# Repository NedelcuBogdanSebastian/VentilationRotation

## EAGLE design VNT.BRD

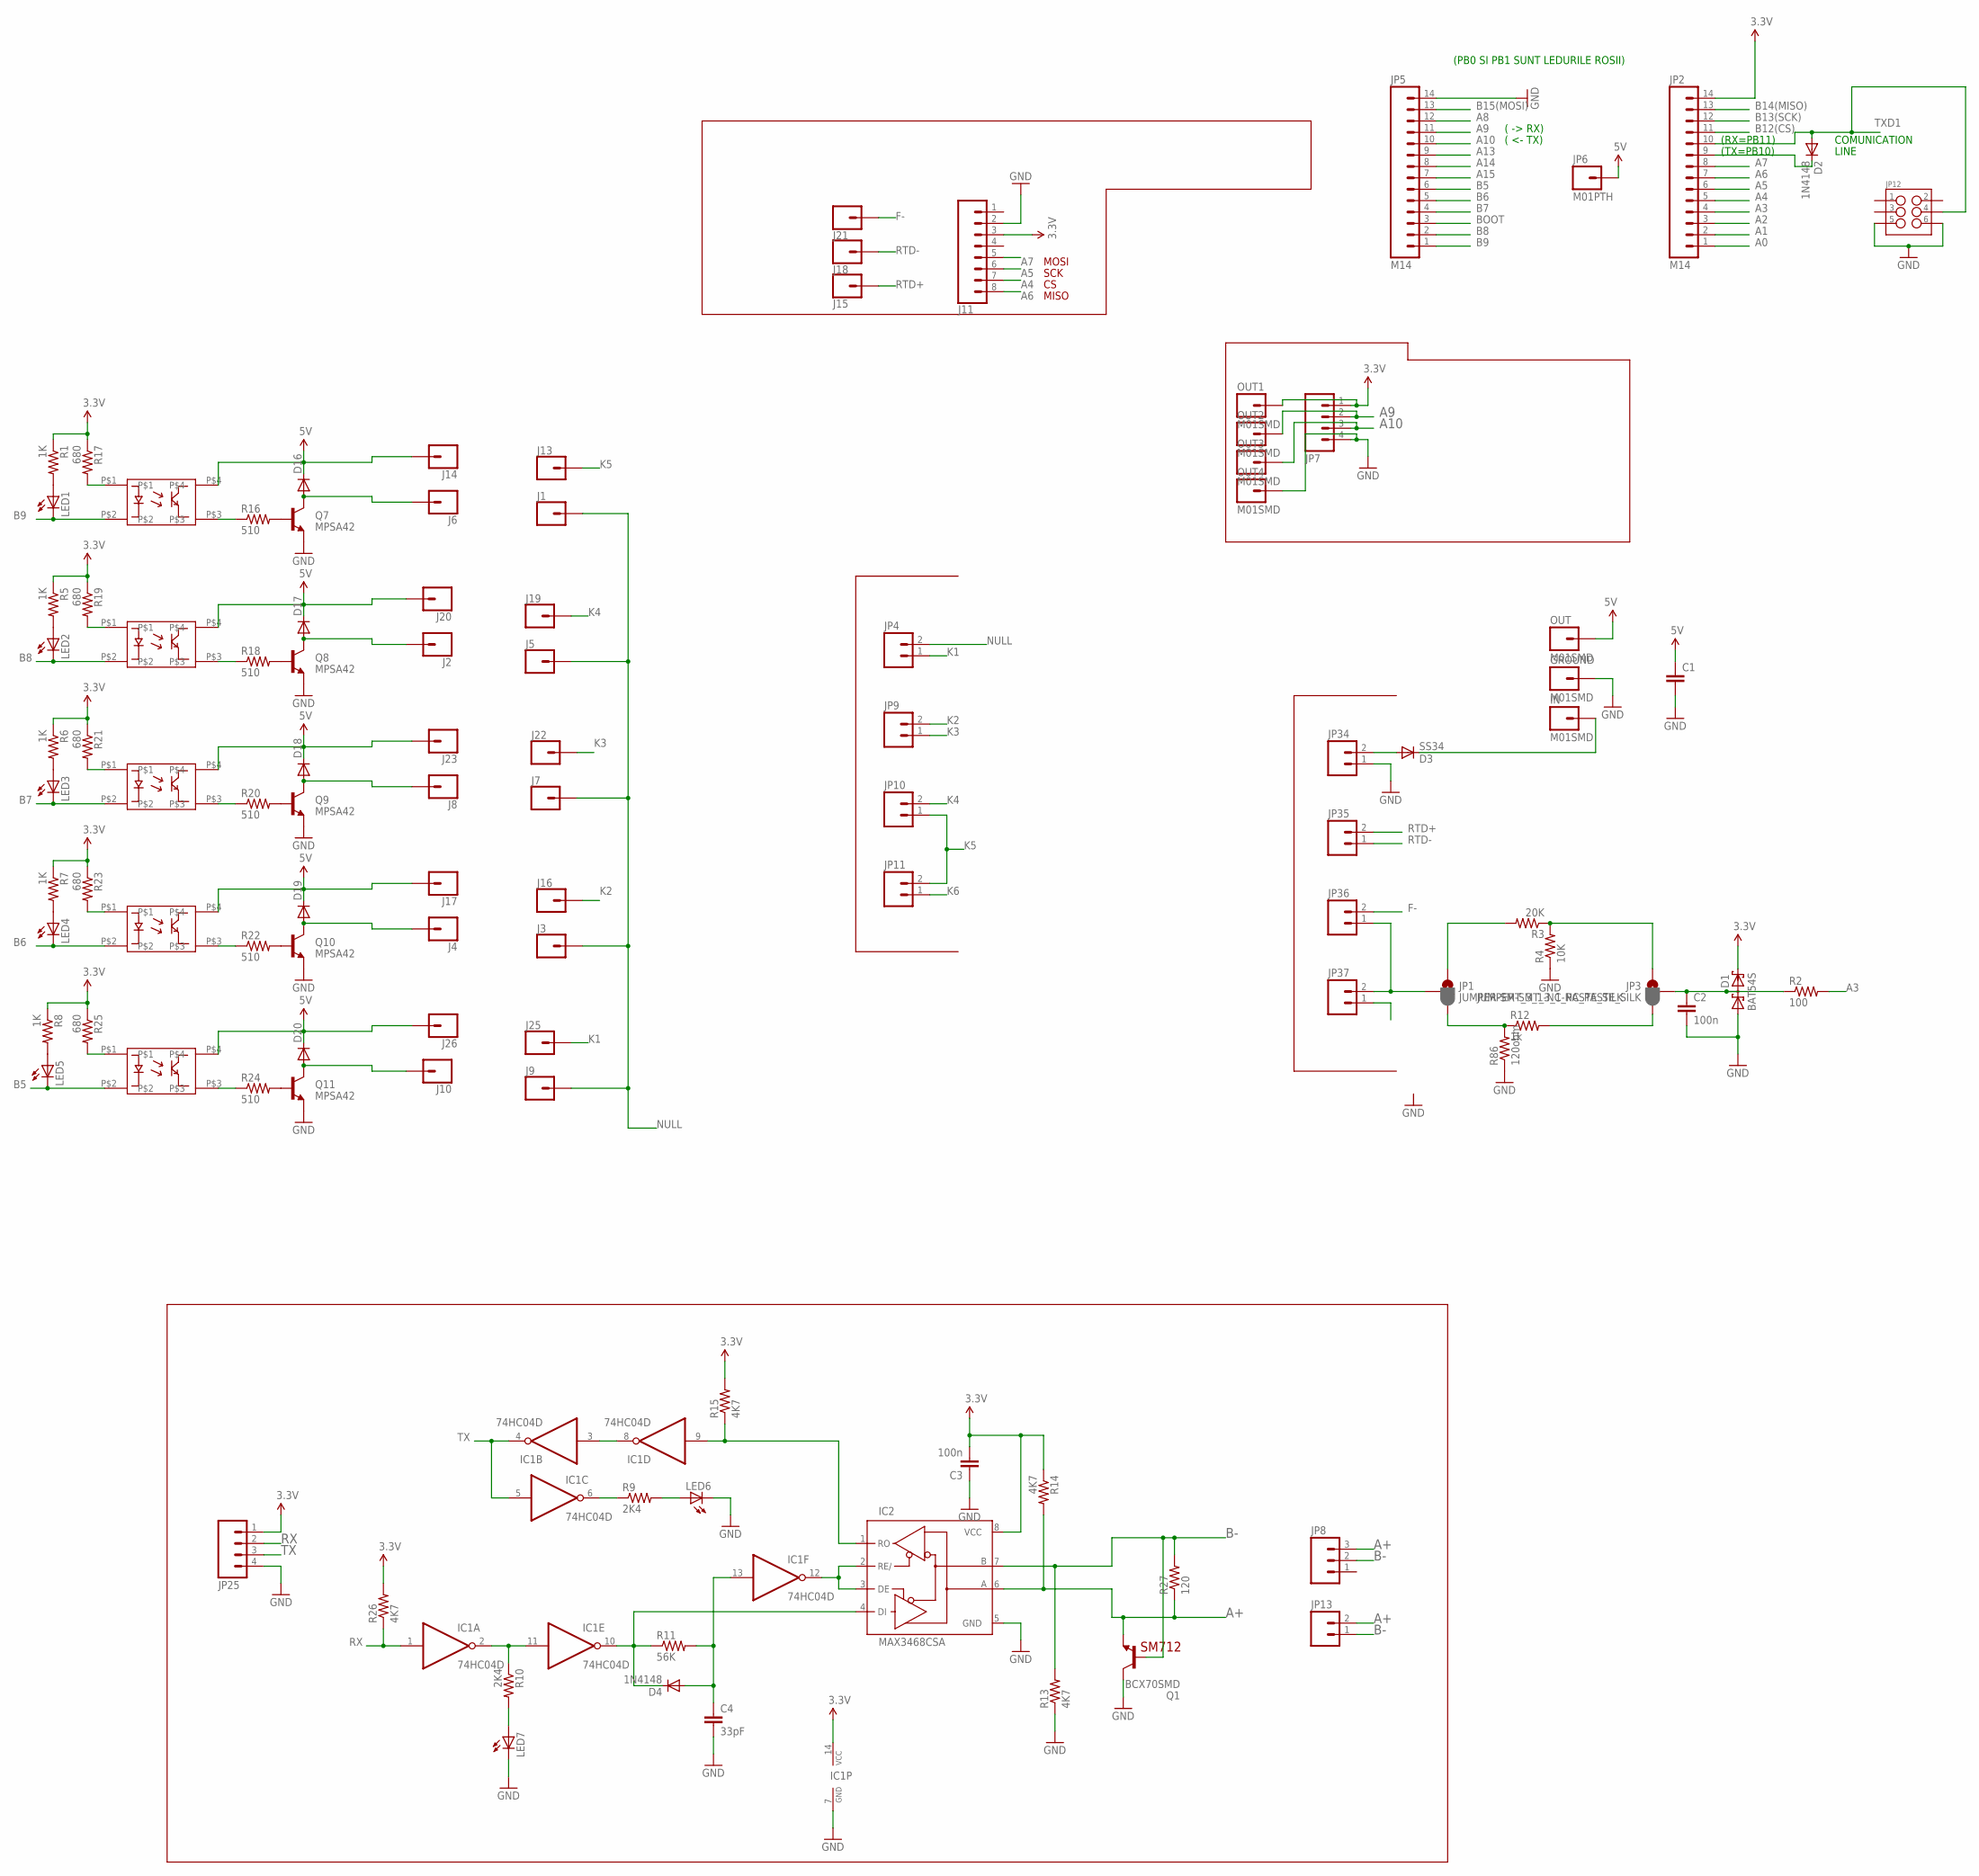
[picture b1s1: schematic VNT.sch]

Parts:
C1: CAPPTH1; CAP-PTH-5MM
C2, C3: 100n; 0805
C4: 33pF; 0805
D1: BAT54S; SOT23
D2, D4: 1N4148; MINIMELF
D3: SS34; SMC
D16, D17, D18, D19, D20: DIODE-MINIMELF; MINIMELF
GROUND: M01SMD; LUXEON-PAD
IC1: 74HC04D; SO14
IC2: MAX3468CSA; SO08
IN: M01SMD; LUXEON-PAD
J1, J2, J3, J4, J5, J6, J7, J8, J9, J10, J13, J14, J15, J16, J17, J18, J19, J20, J21, J22, J23, J25, J26: CONN_01; 1X01@2
J11: CONN_08LOCK; 1X08_LOCK
JP1, JP3: JUMPER-SMT_3_1-NC_PASTE_SILK; SMT-JUMPER_3_1-NC_PASTE_SILK
JP2, JP5: M14; 1X14
JP4, JP9, JP10, JP11, JP13, JP34, JP35, JP36, JP37: M025MM; SCREWTERMINAL-5MM-2
JP6: M01PTH; 1X01
JP7, JP25: M04PTH; 1X04
JP8: M03-SCREW-5MM; SCREWTERMINAL-5MM-3
JP12: M03X22X3_SILK_MALE_PTH; 2X3
LED1, LED2, LED3, LED4, LED5, LED6, LED7: LEDCHIP-LED0805; CHIP-LED0805
OUT, OUT1, OUT2, OUT3, OUT4: M01SMD; LUXEON-PAD
Q1: BCX70SMD; SOT23
Q7, Q8, Q9, Q10, Q11: MPSA42; SOT23-3
R1, R5, R6, R7, R8: 1K; 0805
R2: 100; 0805
R3: 20K; 1206
R4: 10K; 1206
R9, R10: 2K4; 0805
R11: 56K; 0805
R12: 1k; 0805
R13, R14, R15, R26: 4K7; 0805
R16, R18, R20, R22, R24: 510; 0805
R17, R19, R21, R23, R25: 680; 0805
R27: 120; 0805
R86: 120ohm; R2010
U$13, U$14, U$15, U$16, U$17: IS181D-I; TLP181-I

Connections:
3.3V: C3.2, D1.2 (C2), IC1.14 (VCC), IC2.8 (VCC), J11.3, JP2.14, JP7.1, JP25.1, OUT1.P$1, R1.1, R5.1, R6.1, R7.1, R8.1, R14.1, R15.2, R17.1, R19.1, R21.1, R23.1, R25.1, R26.2
5V: C1.1, D16.C, D17.C, D18.C, D19.C, D20.C, J14.1, J17.1, J20.1, J23.1, J26.1, JP6.1, OUT.P$1, U$13.P$4, U$14.P$4, U$15.P$4, U$16.P$4, U$17.P$4
A0: JP2.1
A1: JP2.2
A2: JP2.3
A3: JP2.4, R2.2
A4: J11.7, JP2.5
A5: J11.6, JP2.6
A6: J11.8, JP2.7
A7: J11.5, JP2.8
A8: JP5.12
A9: JP5.11, JP7.2, OUT2.P$1
A10: JP5.10, JP7.3, OUT3.P$1
A13: JP5.9
A14: JP5.8
A15: JP5.7
A+: IC2.6 (A), JP8.3, JP13.2, Q1.2 (E), R14.2, R27.1
B5: JP5.6, LED5.C, U$17.P$2
B6: JP5.5, LED4.C, U$16.P$2
B7: JP5.4, LED3.C, U$15.P$2
B8: JP5.2, LED2.C, U$13.P$2
B9: JP5.1, LED1.C, U$14.P$2
B12(CS): JP2.11
B13(SCK): JP2.12
B14(MISO): JP2.13
B15(MOSI): JP5.13
B-: IC2.7 (B), JP8.2, JP13.1, Q1.1 (B), R13.2, R27.2
BOOT: JP5.3
F-: J21.1, JP36.2
GND: C1.2, C2.2, C3.1, C4.2, D1.1 (A1), GROUND.P$1, IC1.7 (GND), IC2.5 (GND), J11.2, JP5.14, JP7.4, JP12.5, JP12.6, JP25.4, JP34.1, LED6.C, LED7.C, OUT4.P$1, Q1.3 (C), Q7.2 (E), Q8.2 (E), Q9.2 (E), Q10.2 (E), Q11.2 (E), R4.1, R13.1, R86.1
K1: J25.1, JP4.1
K2: J16.1, JP9.2
K3: J22.1, JP9.1
K4: J19.1, JP10.2
K5: J13.1, JP10.1, JP11.2
K6: JP11.1
unnamed: LED1.A, R1.2
unnamed: LED2.A, R5.2
unnamed: LED3.A, R6.2
unnamed: D3.A, JP34.2
unnamed: JP3.3, R12.2
unnamed: JP3.1, R3.1, R4.2
unnamed: C2.1, D1.3 (C1A2), JP3.2, R2.1
unnamed: JP1.1, R3.2
unnamed: LED4.A, R7.2
unnamed: LED5.A, R8.2
unnamed: D3.C, IN.P$1
unnamed: LED7.A, R10.2
unnamed: LED6.A, R9.2
unnamed: IC1.2 (O), IC1.11 (I), R10.1
unnamed: IC1.9 (I), IC2.1 (RO), R15.1
unnamed: JP1.2, JP36.1, JP37.2
unnamed: IC1.3 (I), IC1.8 (O)
unnamed: C4.1, D4.A, IC1.13 (I), R11.2
unnamed: IC1.6 (O), R9.1
unnamed: D4.C, IC1.10 (O), IC2.4 (DI), R11.1
unnamed: IC1.12 (O), IC2.2 (RE/), IC2.3 (DE)
unnamed: Q7.1 (B), R16.2
unnamed: D16.A, J6.1, Q7.3 (C)
unnamed: Q8.1 (B), R18.2
unnamed: D17.A, J2.1, Q8.3 (C)
unnamed: Q9.1 (B), R20.2
unnamed: D18.A, J8.1, Q9.3 (C)
unnamed: Q10.1 (B), R22.2
unnamed: D19.A, J4.1, Q10.3 (C)
unnamed: Q11.1 (B), R24.2
unnamed: D20.A, J10.1, Q11.3 (C)
unnamed: R16.1, U$14.P$3
unnamed: R17.2, U$14.P$1
unnamed: R18.1, U$13.P$3
unnamed: R20.1, U$15.P$3
unnamed: R22.1, U$16.P$3
unnamed: R24.1, U$17.P$3
unnamed: R19.2, U$13.P$1
unnamed: R21.2, U$15.P$1
unnamed: R23.2, U$16.P$1
unnamed: R25.2, U$17.P$1
unnamed: JP1.3, R12.1, R86.2
NULL: J1.1, J3.1, J5.1, J7.1, J9.1, JP4.2
RTD+: J15.1, JP35.2
RTD-: J18.1, JP35.1
RX: IC1.1 (I), JP25.2, R26.1
RXD1: D2.C, JP2.9
TX: IC1.4 (O), IC1.5 (I), JP25.3
TXD1: D2.A, JP2.10, JP12.4

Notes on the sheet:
COMUNICATION
LINE
( -> RX)
( <- TX)
(PB0 SI PB1 SUNT LEDURILE ROSII)
(RX=PB11)
(TX=PB10)
MISO
SCK
MOSI
SM712

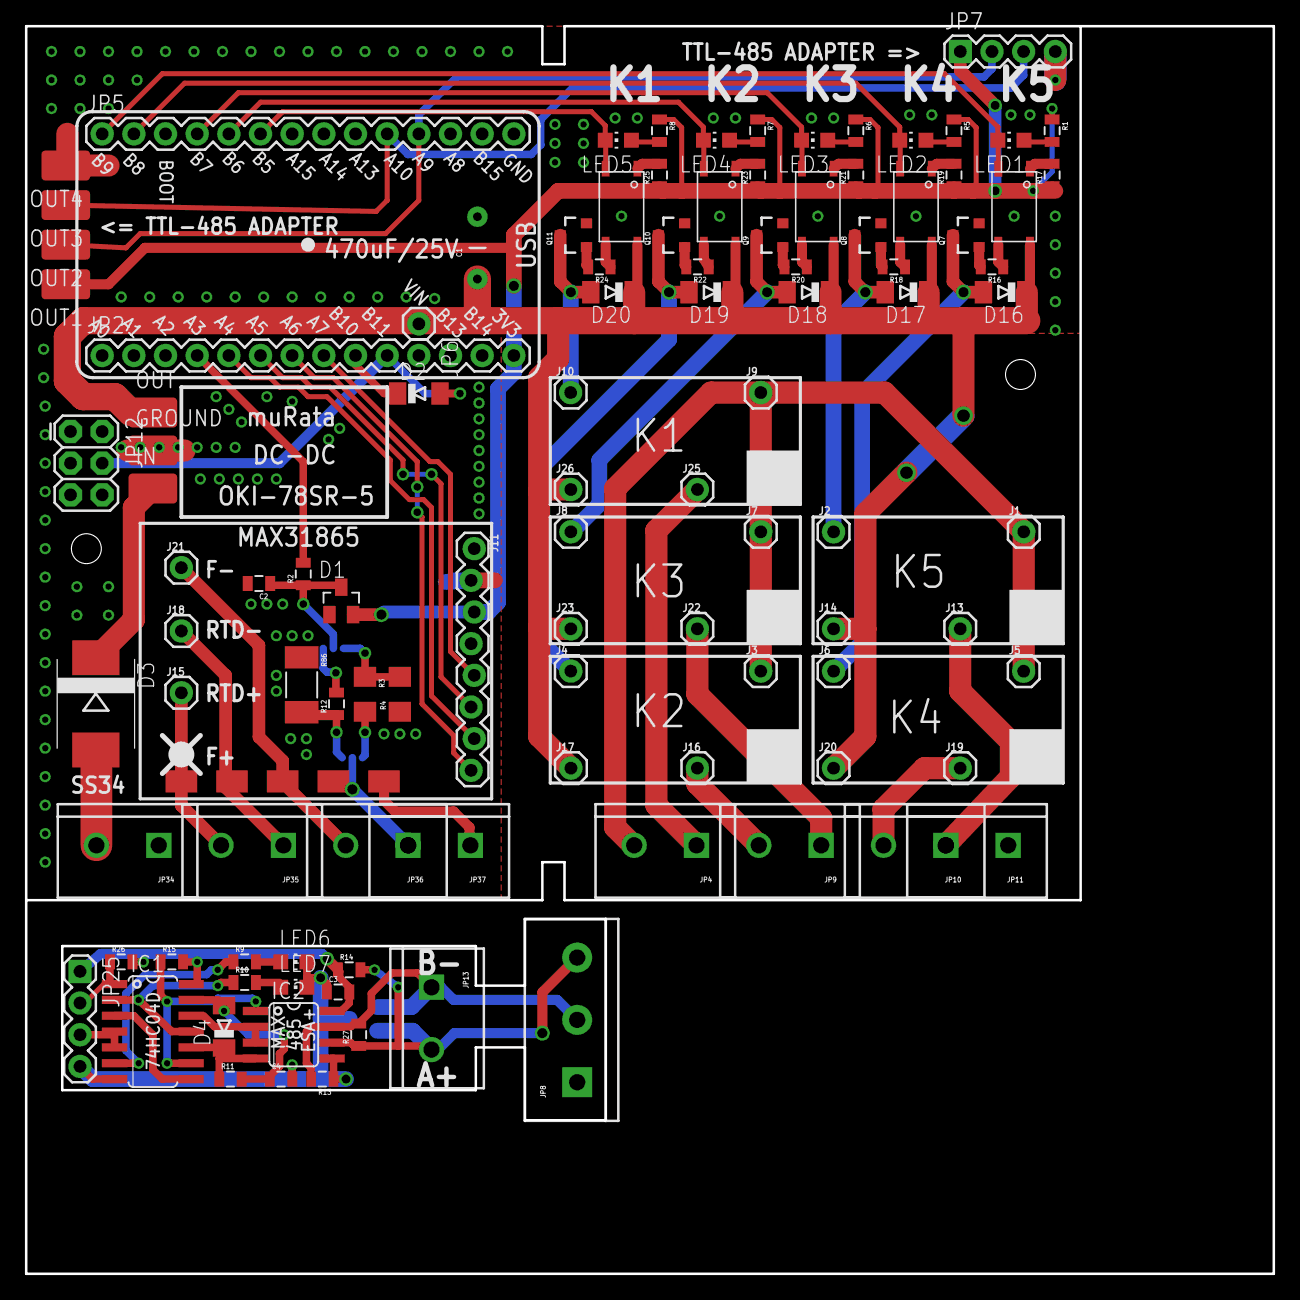
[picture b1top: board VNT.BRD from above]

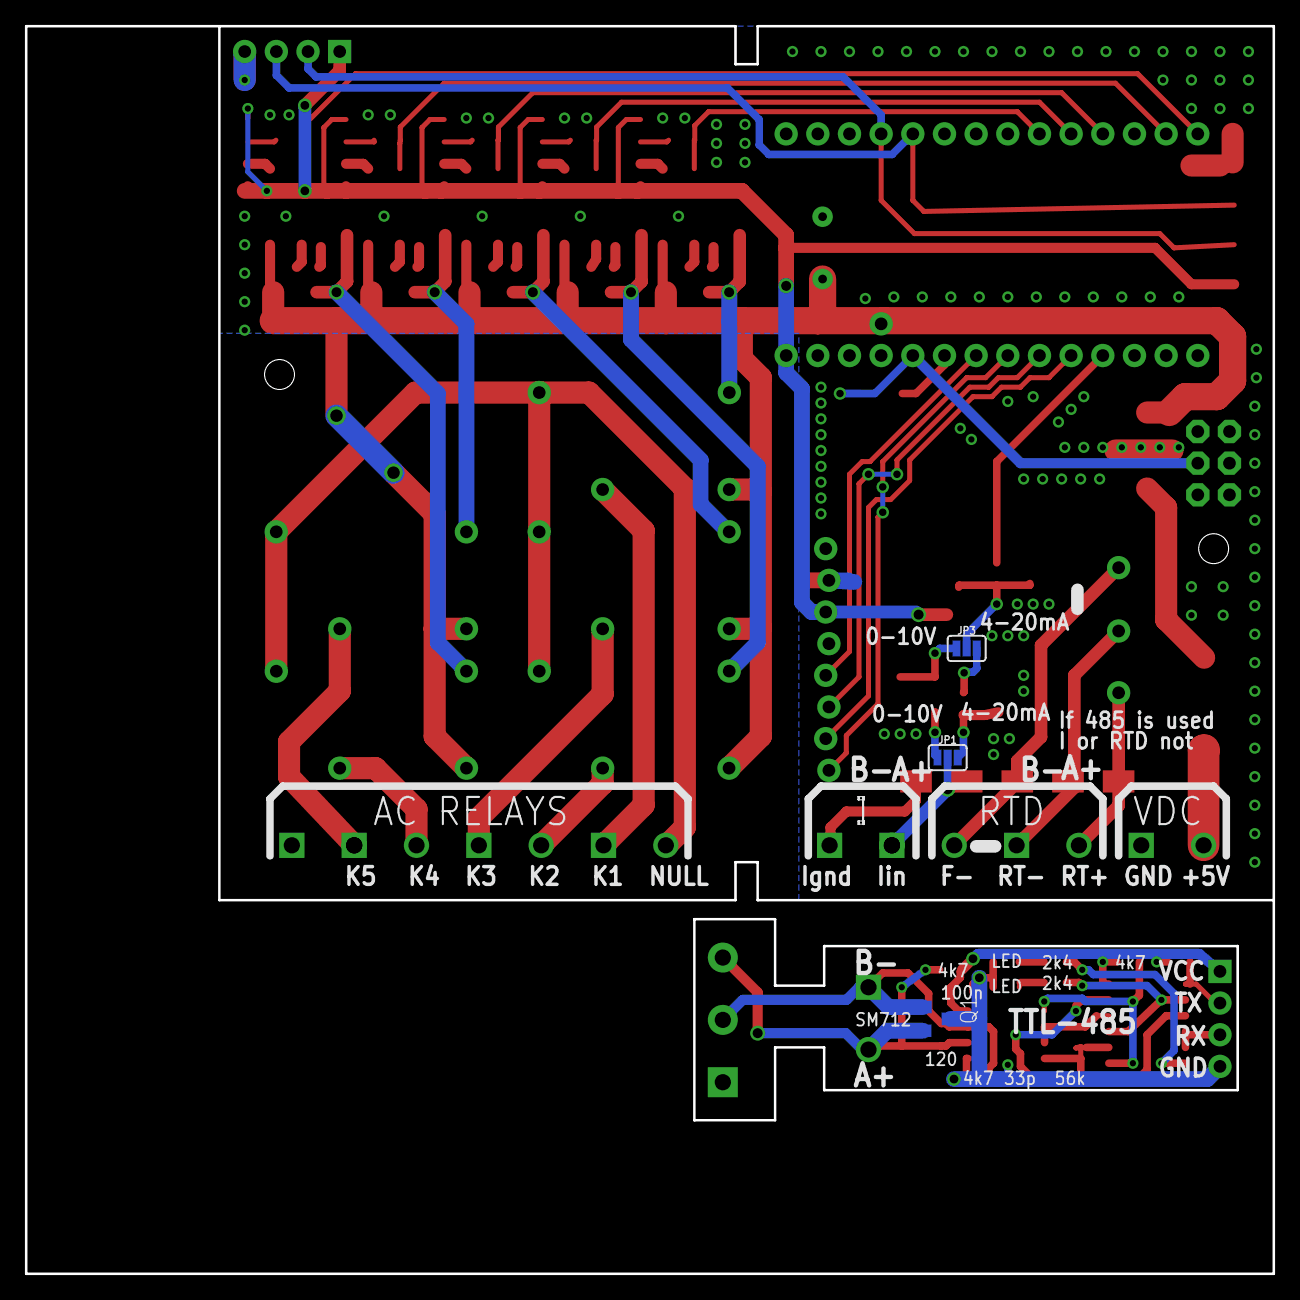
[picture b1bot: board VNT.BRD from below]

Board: 2 copper layers, 100.1 x 100.1 mm, 110 parts (3 on the bottom side), 72 nets.

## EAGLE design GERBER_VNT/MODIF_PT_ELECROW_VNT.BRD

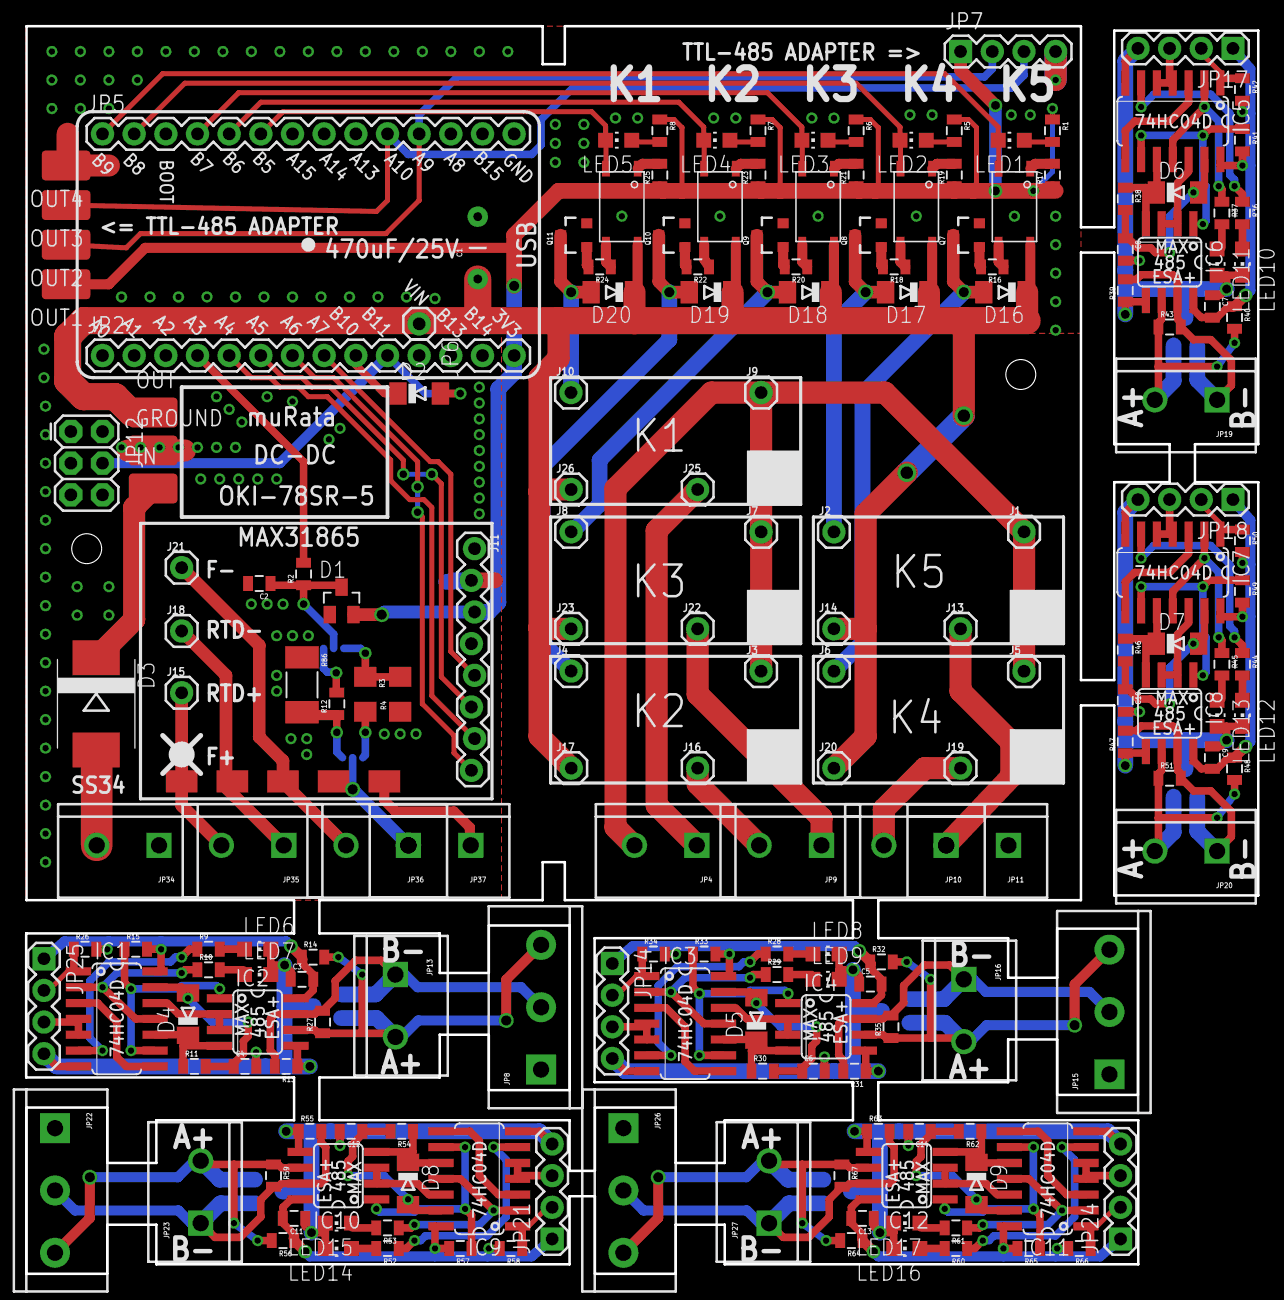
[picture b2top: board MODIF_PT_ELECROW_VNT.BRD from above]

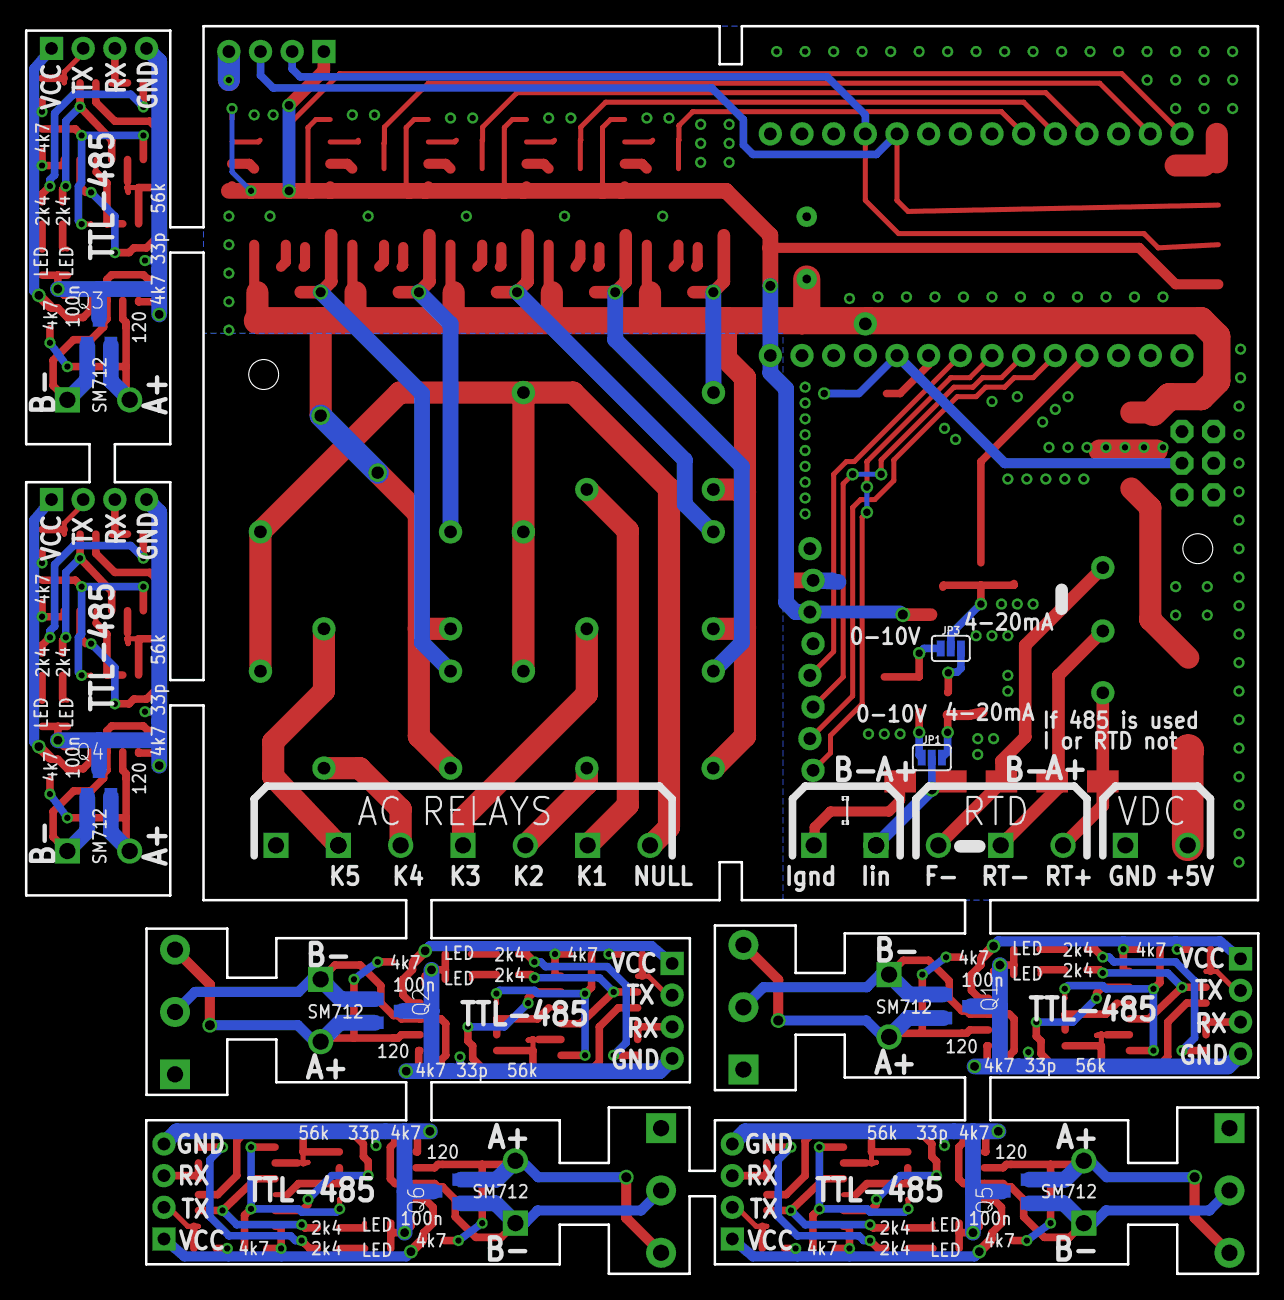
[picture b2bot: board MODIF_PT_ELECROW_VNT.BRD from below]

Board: 2 copper layers, 98.8 x 100.1 mm, 203 parts (8 on the bottom side), 148 nets.

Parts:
C1: CAP-PTH-5MM
C2, C3, C5, C7, C9, C11, C13: 100n; 0805
C4, C6, C8, C10, C12, C14: 33pF; 0805
D1: BAT54S; SOT23
D2, D4, D5, D6, D7, D8, D9: 1N4148; MINIMELF
D3: SS34; SMC
D16, D17, D18, D19, D20: MINIMELF
GROUND: M01SMD; LUXEON-PAD
IC1, IC3, IC5, IC7, IC9, IC11: 74HC04D; SO14
IC2, IC4, IC6, IC8, IC10, IC12: MAX3468CSA; SO08
IN: M01SMD; LUXEON-PAD
J1, J2, J3, J4, J5, J6, J7, J8, J9, J10, J13, J14, J15, J16, J17, J18, J19, J20, J21, J22, J23, J25, J26: 1X01@2
J11: 1X08_LOCK
JP1, JP3: JUMPER-SMT_3_1-NC_PASTE_SILK; SMT-JUMPER_3_1-NC_PASTE_SILK
JP2, JP5: M14; 1X14
JP4, JP9, JP10, JP11, JP13, JP16, JP19, JP20, JP23, JP27, JP34, JP35, JP36, JP37: SCREWTERMINAL-5MM-2
JP6: M01PTH; 1X01
JP7, JP14, JP17, JP18, JP21, JP24, JP25: 1X04
JP8, JP15, JP22, JP26: SCREWTERMINAL-5MM-3
JP12: 2X3
LED1, LED2, LED3, LED4, LED5, LED6, LED7, LED8, LED9, LED10, LED11, LED12, LED13, LED14, LED15, LED16, LED17: CHIP-LED0805
OUT, OUT1, OUT2, OUT3, OUT4: M01SMD; LUXEON-PAD
Q1, Q2, Q3, Q4, Q5, Q6: BCX70SMD; SOT23
Q7, Q8, Q9, Q10, Q11: MPSA42; SOT23-3
R1, R5, R6, R7, R8: 1K; 0805
R2: 100; 0805
R3: 20K; 1206
R4: 10K; 1206
R9, R10, R28, R29, R36, R37, R44, R45, R52, R53, R60, R61: 2K4; 0805
R11, R30, R38, R46, R54, R62: 56K; 0805
R12: 1k; 0805
R13, R14, R15, R26, R31, R32, R33, R34, R39, R40, R41, R42, R47, R48, R49, R50, R55, R56, R57, R58, R63, R64, R65, R66: 4K7; 0805
R16, R18, R20, R22, R24: 510; 0805
R17, R19, R21, R23, R25: 680; 0805
R27, R35, R43, R51, R59, R67: 120; 0805
R86: 120ohm; R2010
U$13, U$14, U$15, U$16, U$17: IS181D-I; TLP181-I

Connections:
3.3V: D1.2, J11.3, JP2.14, JP7.1, OUT1.P$1, R1.1, R5.1, R6.1, R7.1, R8.1, R17.1, R19.1, R21.1, R23.1, R25.1
3.3V1: C5.2, IC3.14, IC4.8, JP14.1, R32.1, R33.2, R34.2
3.3V2: C7.2, IC5.14, IC6.8, JP17.1, R40.1, R41.2, R42.2
3.3V3: C9.2, IC7.14, IC8.8, JP18.1, R48.1, R49.2, R50.2
3.3V4: C11.2, IC9.14, IC10.8, JP21.1, R56.1, R57.2, R58.2
3.3V5: C13.2, IC11.14, IC12.8, JP24.1, R64.1, R65.2, R66.2
5V: C1.1, D16.C, D17.C, D18.C, D19.C, D20.C, J14.1, J17.1, J20.1, J23.1, J26.1, JP6.1, OUT.P$1, U$13.P$4, U$14.P$4, U$15.P$4, U$16.P$4, U$17.P$4
A3: JP2.4, R2.2
A4: J11.7, JP2.5
A5: J11.6, JP2.6
A6: J11.8, JP2.7
A7: J11.5, JP2.8
A9: JP5.11, JP7.2, OUT2.P$1
A10: JP5.10, JP7.3, OUT3.P$1
A+: IC2.6, JP8.3, JP13.2, Q1.2, R14.2, R27.1
A+1: IC4.6, JP15.3, JP16.2, Q2.2, R32.2, R35.1
A+2: IC6.6, JP19.2, Q3.2, R40.2, R43.1
A+3: IC8.6, JP20.2, Q4.2, R48.2, R51.1
A+4: IC10.6, JP22.3, JP23.2, Q5.2, R56.2, R59.1
A+5: IC12.6, JP26.3, JP27.2, Q6.2, R64.2, R67.1
B5: JP5.6, LED5.C, U$17.P$2
B6: JP5.5, LED4.C, U$16.P$2
B7: JP5.4, LED3.C, U$15.P$2
B8: JP5.2, LED2.C, U$13.P$2
B9: JP5.1, LED1.C, U$14.P$2
B-: IC2.7, JP8.2, JP13.1, Q1.1, R13.2, R27.2
B-1: IC4.7, JP15.2, JP16.1, Q2.1, R31.2, R35.2
B-2: IC6.7, JP19.1, Q3.1, R39.2, R43.2
B-3: IC8.7, JP20.1, Q4.1, R47.2, R51.2
B-4: IC10.7, JP22.2, JP23.1, Q5.1, R55.2, R59.2
B-5: IC12.7, JP26.2, JP27.1, Q6.1, R63.2, R67.2
F-: J21.1, JP36.2
GND: C1.2, C2.2, C3.1, C4.2, D1.1, GROUND.P$1, IC1.7, IC2.5, J11.2, JP5.14, JP7.4, JP12.5, JP12.6, JP25.4, JP34.1, LED6.C, LED7.C, OUT4.P$1, Q1.3, Q7.2, Q8.2, Q9.2, Q10.2, Q11.2, R4.1, R13.1, R86.1
GND2: C5.1, C6.2, IC3.7, IC4.5, JP14.4, LED8.C, LED9.C, Q2.3, R31.1
GND3: C7.1, C8.2, IC5.7, IC6.5, JP17.4, LED10.C, LED11.C, Q3.3, R39.1
GND4: C9.1, C10.2, IC7.7, IC8.5, JP18.4, LED12.C, LED13.C, Q4.3, R47.1
GND5: C11.1, C12.2, IC9.7, IC10.5, JP21.4, LED14.C, LED15.C, Q5.3, R55.1
GND6: C13.1, C14.2, IC11.7, IC12.5, JP24.4, LED16.C, LED17.C, Q6.3, R63.1
K1: J25.1, JP4.1
K2: J16.1, JP9.2
K3: J22.1, JP9.1
K4: J19.1, JP10.2
K5: J13.1, JP10.1, JP11.2
unnamed: LED1.A, R1.2
unnamed: LED2.A, R5.2
unnamed: LED3.A, R6.2
unnamed: D3.A, JP34.2
unnamed: JP3.3, R12.2
unnamed: JP3.1, R3.1, R4.2
unnamed: C2.1, D1.3, JP3.2, R2.1
unnamed: JP1.1, R3.2
unnamed: LED4.A, R7.2
unnamed: LED5.A, R8.2
unnamed: D3.C, IN.P$1
unnamed: IC3.9, IC4.1, R33.1
unnamed: IC3.3, IC3.8
unnamed: C6.1, D5.A, IC3.13, R30.2
unnamed: LED7.A, R10.2
unnamed: LED6.A, R9.2
unnamed: IC3.6, R28.1
unnamed: IC1.2, IC1.11, R10.1
unnamed: D5.C, IC3.10, IC4.4, R30.1
unnamed: IC1.9, IC2.1, R15.1
unnamed: JP1.2, JP36.1, JP37.2
unnamed: IC1.3, IC1.8
unnamed: C4.1, D4.A, IC1.13, R11.2
unnamed: IC3.12, IC4.2, IC4.3
unnamed: LED9.A, R29.2
unnamed: IC1.6, R9.1
unnamed: LED8.A, R28.2
unnamed: D4.C, IC1.10, IC2.4, R11.1
unnamed: IC1.12, IC2.2, IC2.3
unnamed: IC3.2, IC3.11, R29.1
unnamed: IC5.9, IC6.1, R41.1
unnamed: IC5.3, IC5.8
unnamed: C8.1, D6.A, IC5.13, R38.2
unnamed: IC5.6, R36.1
unnamed: D6.C, IC5.10, IC6.4, R38.1
unnamed: IC5.12, IC6.2, IC6.3
unnamed: LED11.A, R37.2
unnamed: LED10.A, R36.2
unnamed: IC5.2, IC5.11, R37.1
unnamed: IC7.9, IC8.1, R49.1
unnamed: IC7.3, IC7.8
unnamed: C10.1, D7.A, IC7.13, R46.2
unnamed: IC7.6, R44.1
unnamed: D7.C, IC7.10, IC8.4, R46.1
unnamed: IC7.12, IC8.2, IC8.3
unnamed: LED13.A, R45.2
unnamed: LED12.A, R44.2
unnamed: IC7.2, IC7.11, R45.1
unnamed: IC9.9, IC10.1, R57.1
unnamed: IC9.3, IC9.8
unnamed: C12.1, D8.A, IC9.13, R54.2
unnamed: Q7.1, R16.2
unnamed: D16.A, J6.1, Q7.3
unnamed: Q8.1, R18.2
unnamed: D17.A, J2.1, Q8.3
unnamed: Q9.1, R20.2
unnamed: D18.A, J8.1, Q9.3
unnamed: Q10.1, R22.2
unnamed: D19.A, J4.1, Q10.3
unnamed: Q11.1, R24.2
unnamed: D20.A, J10.1, Q11.3
unnamed: IC9.6, R52.1
unnamed: D8.C, IC9.10, IC10.4, R54.1
unnamed: IC9.12, IC10.2, IC10.3
unnamed: LED15.A, R53.2
unnamed: LED14.A, R52.2
unnamed: IC9.2, IC9.11, R53.1
unnamed: IC11.9, IC12.1, R65.1
unnamed: IC11.3, IC11.8
unnamed: C14.1, D9.A, IC11.13, R62.2
unnamed: IC11.6, R60.1
unnamed: D9.C, IC11.10, IC12.4, R62.1
unnamed: IC11.12, IC12.2, IC12.3
unnamed: LED17.A, R61.2
unnamed: LED16.A, R60.2
unnamed: R16.1, U$14.P$3
unnamed: R17.2, U$14.P$1
unnamed: IC11.2, IC11.11, R61.1
unnamed: R18.1, U$13.P$3
unnamed: R20.1, U$15.P$3
unnamed: R22.1, U$16.P$3
unnamed: R24.1, U$17.P$3
unnamed: R19.2, U$13.P$1
unnamed: R21.2, U$15.P$1
unnamed: R23.2, U$16.P$1
unnamed: R25.2, U$17.P$1
unnamed: JP1.3, R12.1, R86.2
NULL: J1.1, J3.1, J5.1, J7.1, J9.1, JP4.2
RTD+: J15.1, JP35.2
RTD-: J18.1, JP35.1
RX: IC1.1, JP25.2, R26.1
RX1: IC3.1, JP14.2, R34.1
RX2: IC5.1, JP17.2, R42.1
RX3: IC7.1, JP18.2, R50.1
RX4: IC9.1, JP21.2, R58.1
RX5: IC11.1, JP24.2, R66.1
RXD1: D2.C, JP2.9
S$1: C3.2, IC1.14, IC2.8, JP25.1, R14.1, R15.2, R26.2
TX: IC1.4, IC1.5, JP25.3
TX1: IC3.4, IC3.5, JP14.3
TX2: IC5.4, IC5.5, JP17.3
TX3: IC7.4, IC7.5, JP18.3
TX4: IC9.4, IC9.5, JP21.3
TX5: IC11.4, IC11.5, JP24.3
TXD1: D2.A, JP2.10, JP12.4

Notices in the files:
parts and their libraries:
SparkFun-Connectors: Licensing: CC v3.0 Share-Alike You are welcome to use this library for commercial purposes.
SparkFun-Passives: Licensing: Creative Commons ShareAlike 4.0 International - https://creativecommons.org/licenses/by-sa/4.0
